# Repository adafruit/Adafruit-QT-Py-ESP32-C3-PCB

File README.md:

## Adafruit QT Py ESP32-C3 WiFi Dev Board with STEMMA QT PCB

<a href="http://www.adafruit.com/products/5405"><br/>
Click here to purchase one from the Adafruit shop</a>

PCB files for the Adafruit QT Py ESP32-C3 WiFi Dev Board with STEMMA QT. 

Format is EagleCAD schematic and board layout
* https://www.adafruit.com/product/5405

### Description

What's life without a little RISC? This miniature dev board is perfect for small projects: it comes with our favorite connector - the STEMMA QT, a chainable I2C port, WiFi, Bluetooth LE, and plenty of FLASH and RAM memory for many IoT projects. What a cutie pie! Or is it... a QT Py? This diminutive dev board comes with a RISC-V IoT microcontroller, the ESP32-C3!

ESP32-C3 is a low-cost microcontroller from Espressif that supports 2.4 GHz Wi-Fi and Bluetooth® Low Energy (Bluetooth LE). It has built-in USB-to-Serial, but not native USB - it cannot act as a keyboard or disk drive. The chip used here has 4MB of Flash memory, 400 KB of SRAM and can easily handle TLS connections.

The ESP32-C3 integrates a rich set of peripherals, ranging from UART, I2C, I2S, remote control peripheral, LED PWM controller, general DMA controller, TWAI controller, USB Serial/JTAG controller, temperature sensor, and ADC. It also includes SPI, Dual SPI, and Quad SPI interfaces. There is no DAC or native capacitive touch.

There's a minimum number of pins on this chip, it's specifically designed to be low cost and for simpler projects than ESP32-Sx or ESP32 classics with their large number of GPIO. Think of it more as an intended replacement to the ESP8266 than to the ESP32!

With its state-of-the-art power and RF performance, this SoC is an ideal choice for a wide variety of application scenarios relating to the Internet of Things (IoT), wearable electronics, and smart homes.

### License

Adafruit invests time and resources providing this open source design, please support Adafruit and open-source hardware by purchasing products from [Adafruit](https://www.adafruit.com)!

Designed by Limor Fried/Ladyada for Adafruit Industries.

Creative Commons Attribution/Share-Alike, all text above must be included in any redistribution. 
See license.txt for additional details.

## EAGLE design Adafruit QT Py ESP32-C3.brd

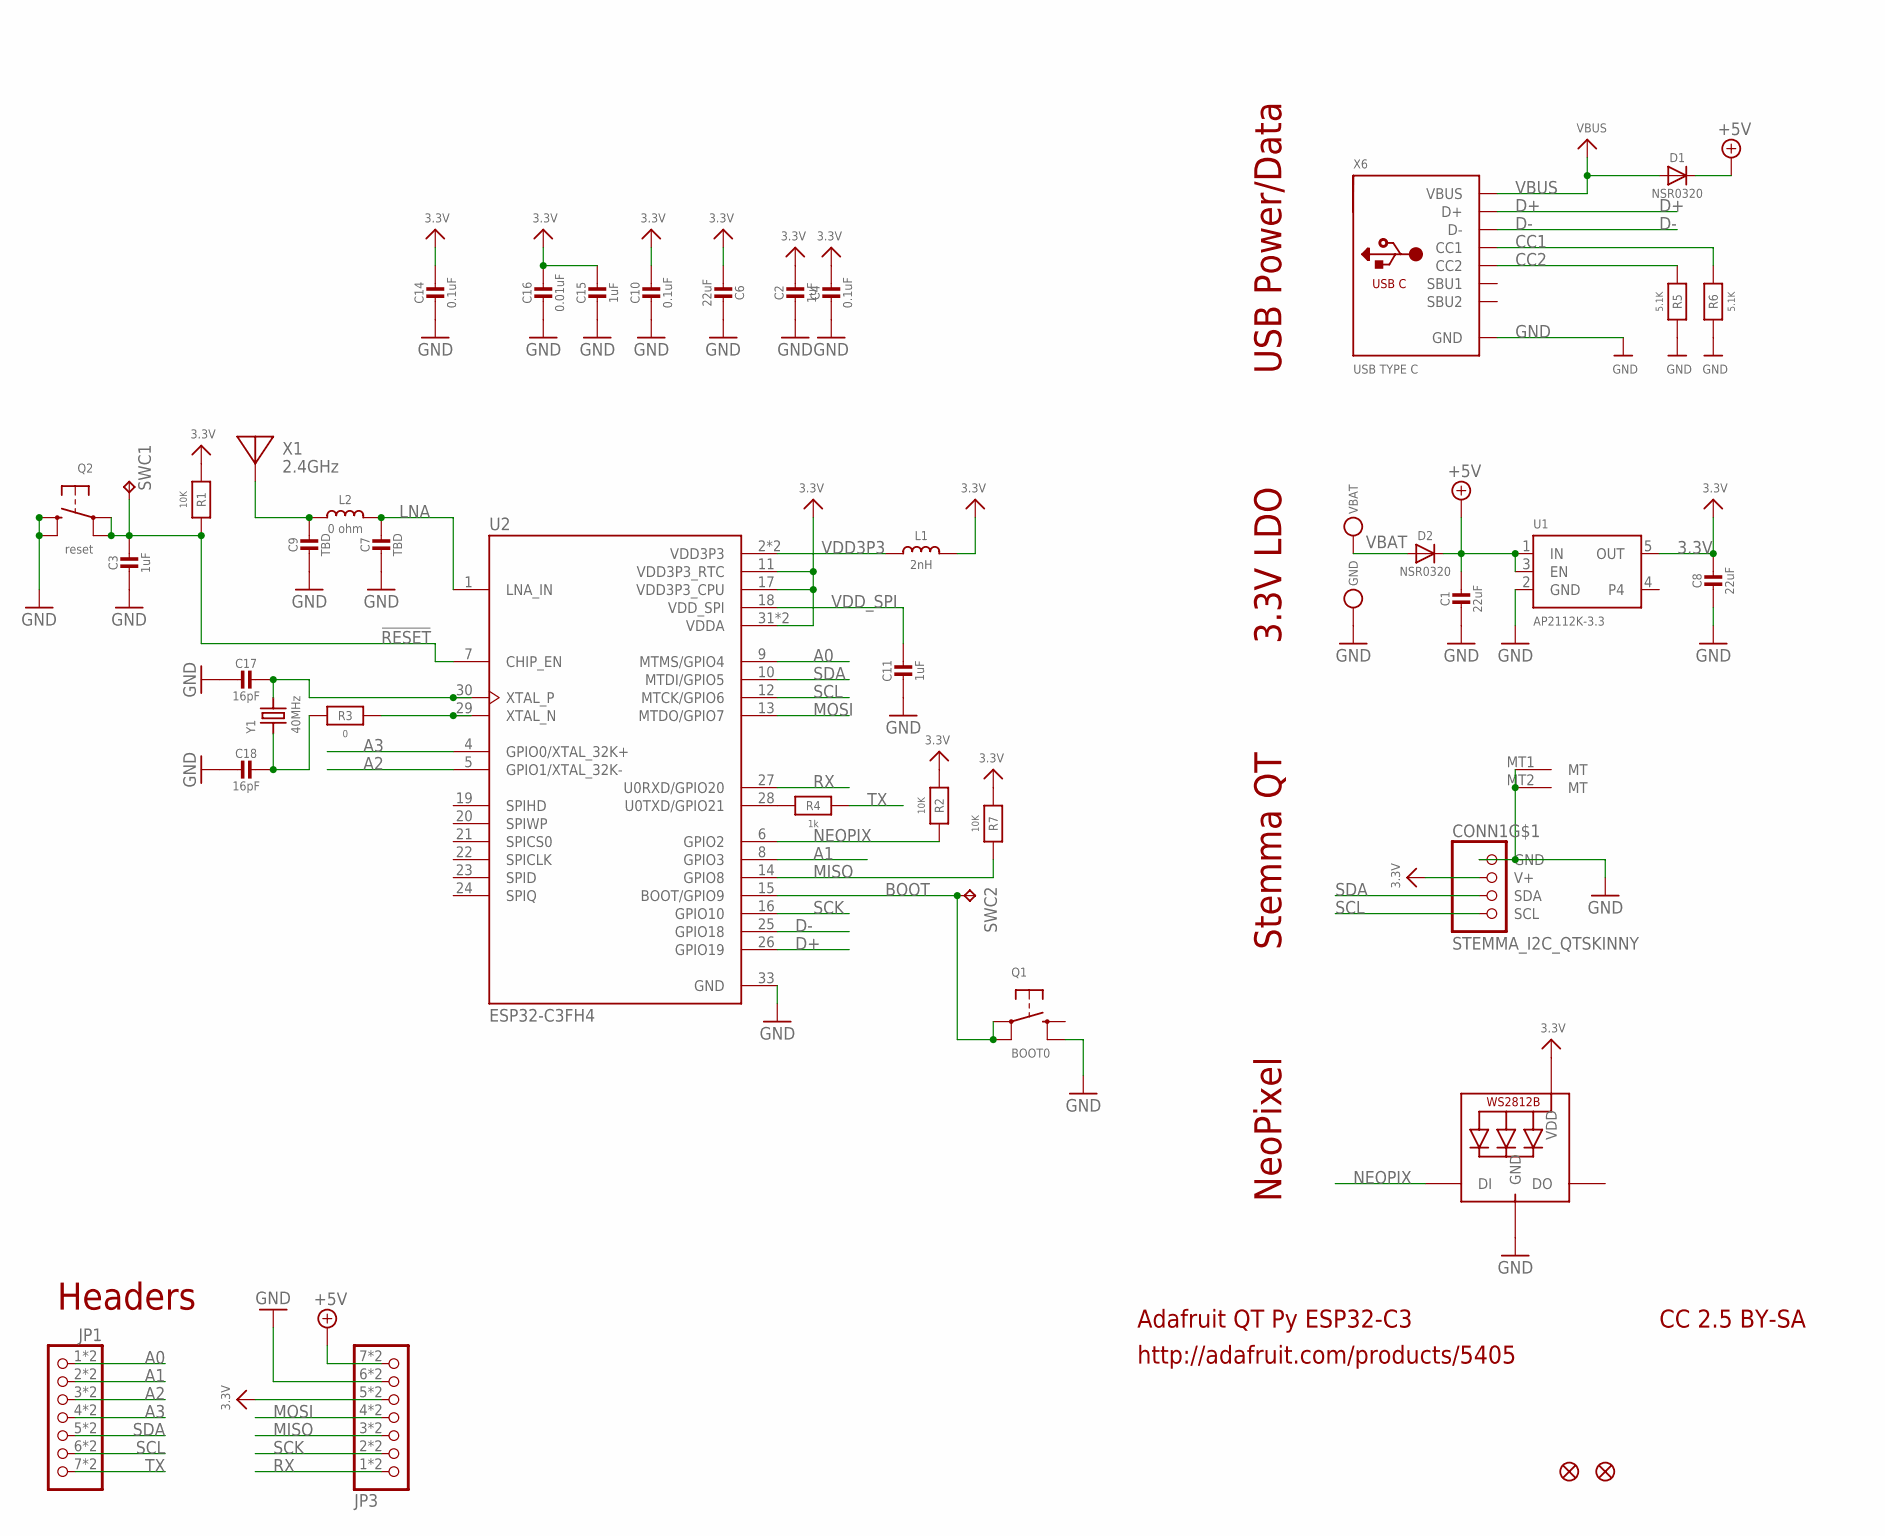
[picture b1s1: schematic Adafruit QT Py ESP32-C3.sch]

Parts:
C1, C6, C8: 22uF; 0805-NO
C2, C3, C11, C15: 1uF; _0402NO
C4, C10, C14: 0.1uF; _0402NO
C7, C9: TBD; _0402NO
C16: 0.01uF; _0402NO
C17, C18: 16pF; _0402NO
CONN1: STEMMA_I2C_QTSKINNY; JST_SH4_SKINNY
D1, D2: NSR0320; SOD-323_MINI
GND: TESTPOINT_MINUS; TESTPOINT_MINUS_1X3MM
JP1, JP3: HEADER-1X7_CASTEL; 1X07_CASTEL
L1: 2nH; _0402
L2: 0 ohm; _0402
LED1: WS2812B_SK6805_1515; SK6805_1515
Q1: BOOT0; BTN_KMR2_4.6X2.8
Q2: reset; BTN_KMR2_SLIM
R1, R2: 10K; _0402NO
R3: 0; _0402NO
R4: 1k; _0402NO
R5, R6: 5.1K; _0402NO
R7: 10K; _0603MP_TWO6MIL
SWC1, SWC2: TPB1,27; B1,27
U1: AP2112K-3.3; SOT23-5
U2: ESP32-C3FH4; QFN32_5MM
U$6, U$8: FIDUCIAL_1MM
VBAT: TESTPOINT_PLUS13; TESTPOINT_PLUS_1X3MM
X1: 2.4GHz; ANT_2450AT18B100
X6: USB TYPE C; USB_C_CUSB31-CFM2AX-01-X
Y1: 40MHz; CRYSTAL_2X1.6

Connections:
3.3V: C2.1, C4.1, C6.1, C8.1, C10.1, C14.1, C15.1, C16.1, CONN1.2 (V+), JP3.5, JP3.5C (5), L1.1, LED1.2 (VDD), R1.1, R2.1, R7.1, U1.5 (OUT), U2.11 (VDD3P3_RTC), U2.17 (VDD3P3_CPU), U2.31 (VDDA), U2.32 (VDDA)
!RESET: C3.1, Q2.A, Q2.A' (P1), R1.2, SWC1.TP, U2.7 (CHIP_EN)
+5V: C1.1, D1.C, D2.C, JP3.7, JP3.7C (7), U1.1 (IN), U1.3 (EN)
A0: JP1.1, JP1.1C (1), U2.9 (MTMS/GPIO4)
A1: JP1.2, JP1.2C (2), U2.8 (GPIO3)
A2: JP1.3, JP1.3C (3), U2.5 (GPIO1/XTAL_32K-)
A3: JP1.4, JP1.4C (4), U2.4 (GPIO0/XTAL_32K+)
BOOT: Q1.A, Q1.A' (P1), SWC2.TP, U2.15 (BOOT/GPIO9)
CC1: R6.2, X6.A5 (CC1)
CC2: R5.2, X6.B5 (CC2)
D+: U2.26 (GPIO19), X6.A6 (D+), X6.B6 (D+)
D-: U2.25 (GPIO18), X6.A7 (D-), X6.B7 (D-)
GND: C1.2, C2.2, C3.2, C4.2, C6.2, C7.2, C8.2, C9.2, C10.2, C11.2, C14.2, C15.2, C16.2, C17.2, C18.2, CONN1.1 (GND), CONN1.MT1 (MT), CONN1.MT2 (MT), GND.P$1, JP3.6, JP3.6C (6), LED1.4 (GND), Q1.B' (S1), Q2.B (S), Q2.B' (S1), R5.1, R6.1, U1.2 (GND), U2.33 (GND), X6.A1B12 (GND), X6.B1A12 (GND)
LNA: C7.1, L2.2, U2.1 (LNA_IN)
MISO: JP3.3, JP3.3C (3), R7.2, U2.14 (GPIO8)
MOSI: JP3.4, JP3.4C (4), U2.13 (MTDO/GPIO7)
unnamed: R4.1, U2.28 (U0TXD/GPIO21)
unnamed: C9.1, L2.1, X1.FP
unnamed: R3.2, U2.29 (XTAL_N)
unnamed: C17.1, U2.30 (XTAL_P), Y1.3 (2)
unnamed: C18.1, R3.1, Y1.1
NEOPIX: LED1.1 (DI), R2.2, U2.6 (GPIO2)
RX: JP3.1, JP3.1C (1), U2.27 (U0RXD/GPIO20)
SCK: JP3.2, JP3.2C (2), U2.16 (GPIO10)
SCL: CONN1.4 (SCL), JP1.6, JP1.6C (6), U2.12 (MTCK/GPIO6)
SDA: CONN1.3 (SDA), JP1.5, JP1.5C (5), U2.10 (MTDI/GPIO5)
TX: JP1.7, JP1.7C (7), R4.2
VBAT: D2.A, VBAT.P$1
VBUS: D1.A, X6.A4B9 (VBUS), X6.B4A9 (VBUS)
VDD3P3: L1.2, U2.2 (VDD3P3), U2.3 (VDD3P3)
VDD_SPI: C11.1, U2.18 (VDD_SPI)

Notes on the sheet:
Adafruit QT Py ESP32-C3
http://adafruit.com/products/5405
CC 2.5 BY-SA
NeoPixel
Stemma QT
3.3V LDO
USB Power/Data
Headers

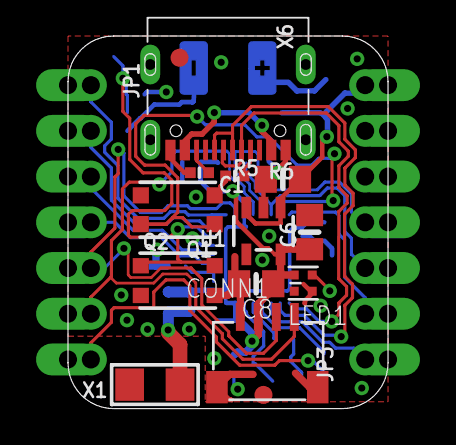
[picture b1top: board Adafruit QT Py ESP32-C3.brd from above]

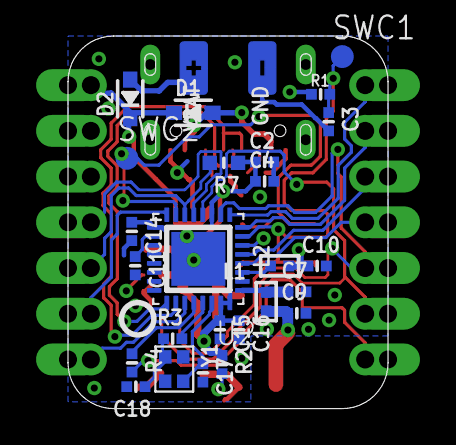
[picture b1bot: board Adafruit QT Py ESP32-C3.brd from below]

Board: 2 copper layers, 17.8 x 20.7 mm, 46 parts (29 on the bottom side), 31 nets.

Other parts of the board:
U$3: QTPYC3_TOP
U$12: PCBFEAT-REV-040
U$18: QTPYC3_BOT

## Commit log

2022-03-14 Initial commit - added pcb files
2022-04-06 Replaced PrettyPins with better cropped version
2024-04-23 Correct the NeoPixel Arduino name

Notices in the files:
parts and their libraries:
microbuilder: This work is placed in the public domain, and may be freely used for commercial and non-commercial work with the following conditions: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
